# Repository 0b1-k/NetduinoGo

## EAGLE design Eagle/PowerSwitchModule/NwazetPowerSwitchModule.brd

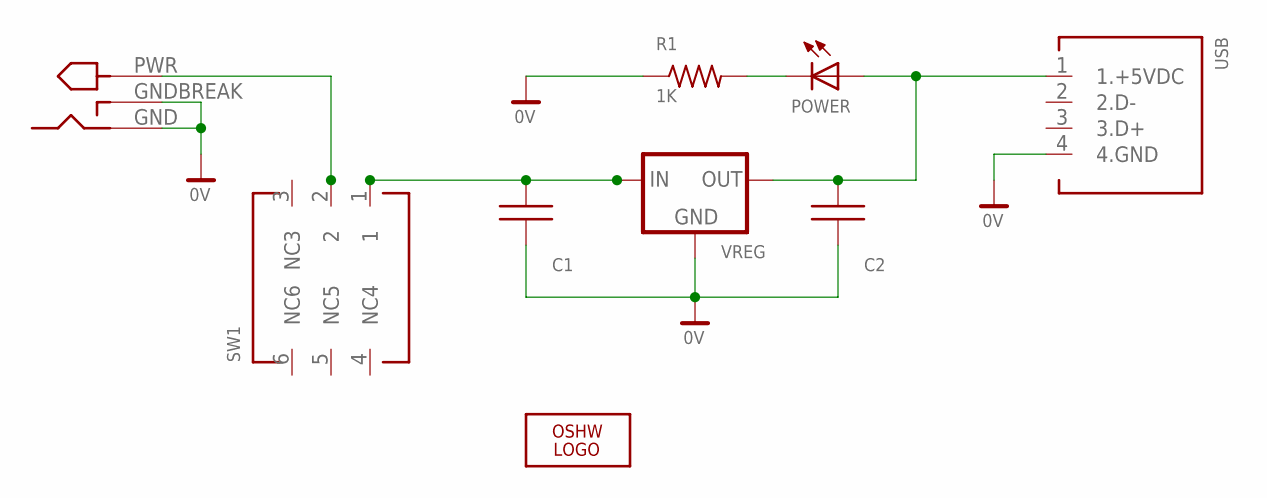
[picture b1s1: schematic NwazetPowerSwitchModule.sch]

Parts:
C1: 0.47uF; 0805
C2: MURATA_GRM_10UF_CER_0805; 0805
LOGO1: OSHW_LOGO_FILLX0100-NT; OSHW_FILLX100_NOTEXT
PJ: CUI_POWER_JACK_102A; CUI_PJ-102A
POWER: LITEON_WHITE_LED_0805; 0805
R1: 1K; 0805
SW1: CTS_065T_SPST_SLIDE_SWITCH
USB: AMPHENOL_USB_TYPE_A_FEMALE_CONNECTOR; USB_CONNECTOR_TYPE_A_FEMALE
VREG: ON_MC33269_800MA_VREG; 800MA_VREG_DPAK

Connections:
+5VDC: C2.K (2), POWER.A, USB.1 (1.+5VDC), VREG.2.VOUT (OUT)
GND: C1.A (1), C2.A (1), PJ.GND, PJ.GNDBREAK, R1.A (1), USB.4 (4.GND), VREG.1.GND_ADJ (GND)
unnamed: POWER.K (C), R1.K (2)
PWR: PJ.PWR, SW1.2
PWR_ON: C1.K (2), SW1.1, VREG.3.VIN (IN)

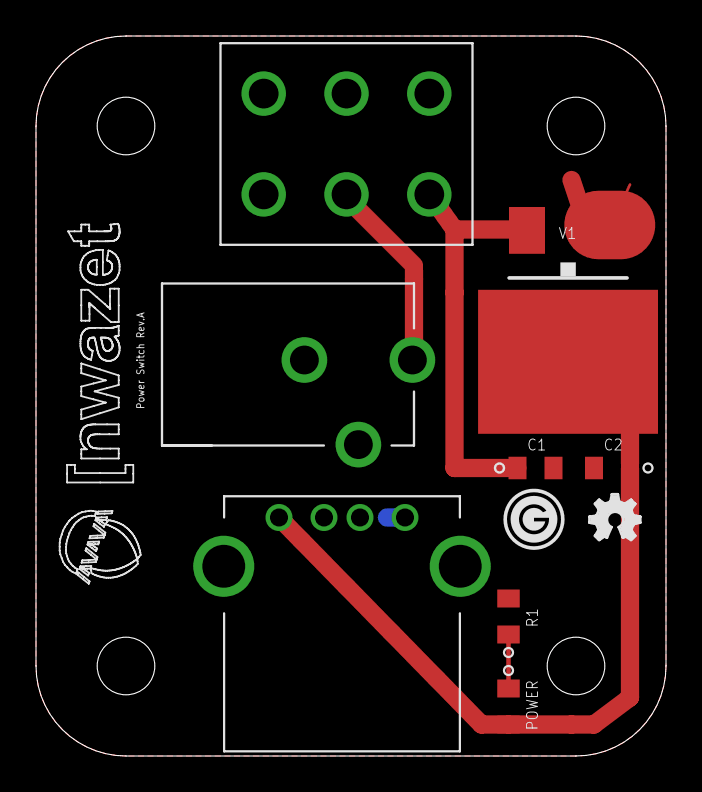
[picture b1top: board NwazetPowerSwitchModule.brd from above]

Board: 2 copper layers, 35.0 x 40.0 mm, 10 parts (0 on the bottom side), 5 nets.

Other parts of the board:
U$1: GO_LOGO

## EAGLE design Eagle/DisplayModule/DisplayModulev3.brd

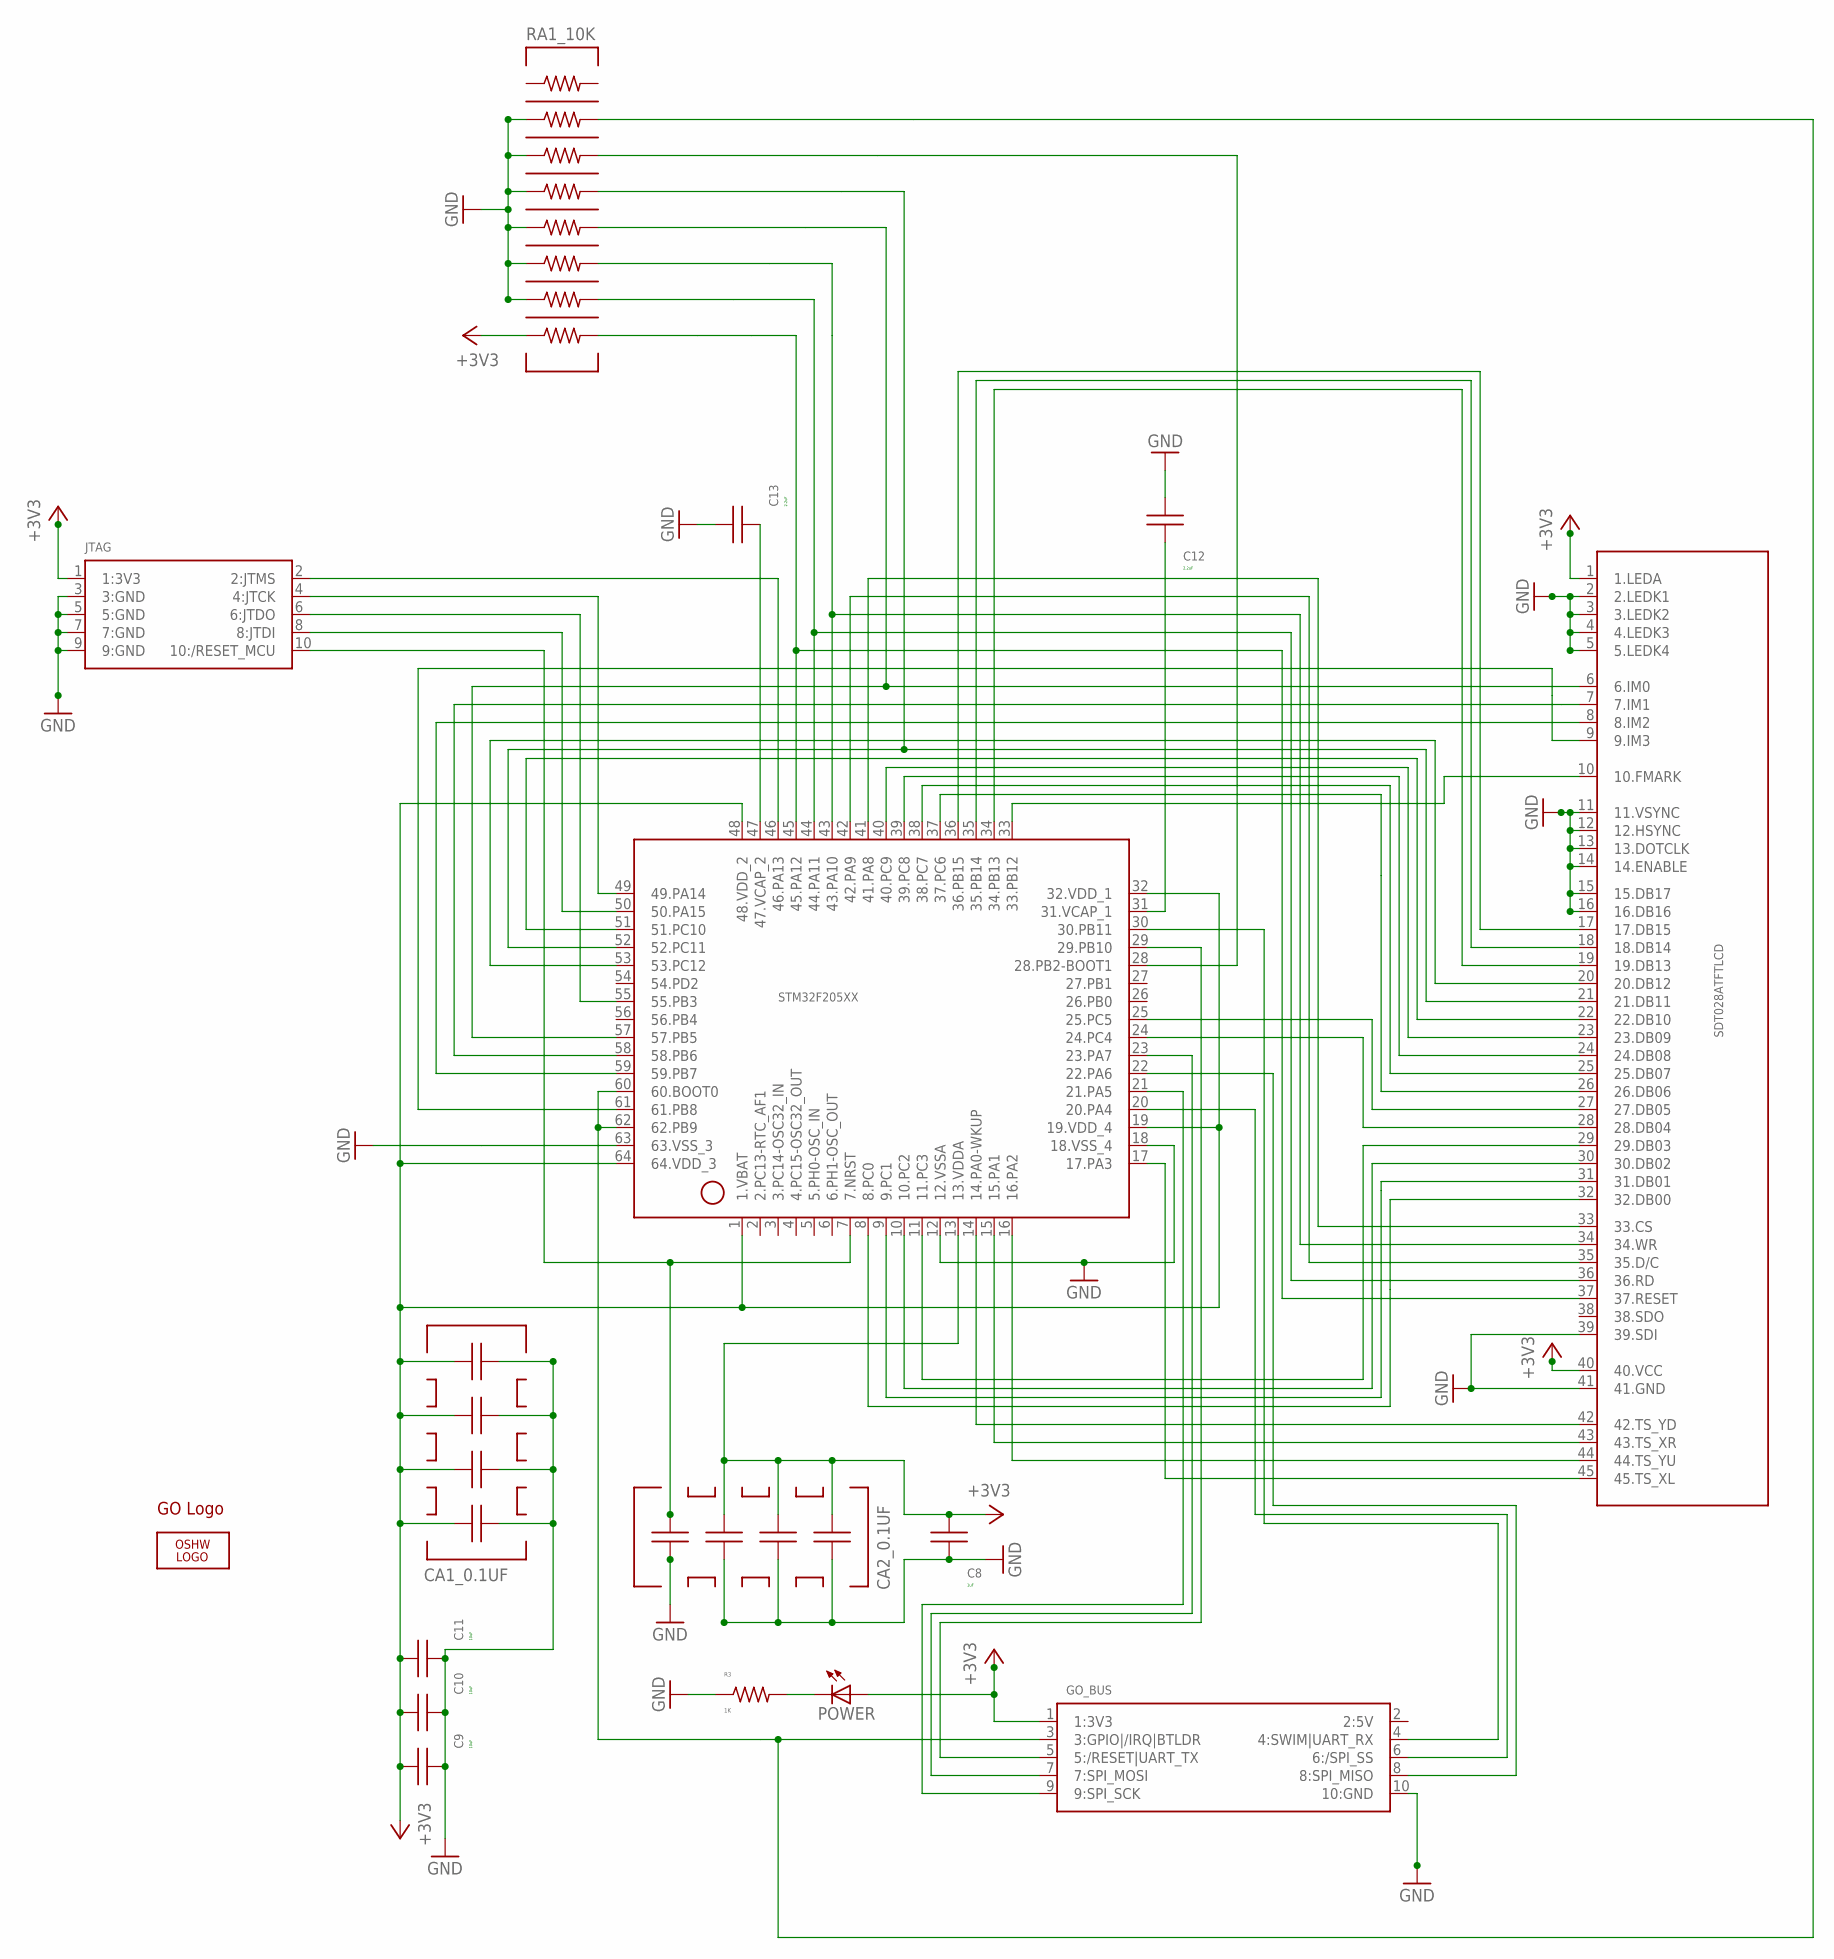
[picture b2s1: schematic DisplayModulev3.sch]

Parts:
C8: 1UF; 0805
C9, C10, C11: 10UF; 0805
C12, C13: 2.2UF; 0805
CA1_0.1UF, CA2_0.1UF: TAYIO-YUDEN_0.1UF_CAP_ARRAY_0805; TAYIO-YUDEN_CAP_ARRAY_4_CIRCUITS_0805
GO_BUS: GO_CONNECTOR; FCI-1.27X1.27MM_10PIN_HEADER_SHROUDED_SMT
JTAG: FCI-MINI_JTAG_HEADER; FCI-MINI_JTAG_CONNECTOR
LOGO1: OSHW_LOGO_FILLX0150-NT; OSHW_FILLX150_NOTEXT
POWER: LITEON_WHITE_LED_0805; 0805
R3: 1K; 0805
RA1_10K: 10K; CTS_742C163_RES_ARRAY_8_CIRCUITS_0603
SDT028ATFTLCD: HIROSE-FH12; HIROSE-FH12S-45S-0.5SH
STM32F205XX: STM32F205XXCORTEXM3RET; STM32F205XX_LQFP64
U$1: GO_LOGO

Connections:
2:5V: GO_BUS.2 (2:5V)
+3V3: C8.K (2), C9.K (2), C10.K (2), C11.K (2), CA1_0.1UF.2, CA1_0.1UF.4, CA1_0.1UF.6, CA1_0.1UF.8, CA2_0.1UF.1, CA2_0.1UF.3, CA2_0.1UF.7, GO_BUS.1 (1:3V3), JTAG.1 (1:3V3), POWER.A, RA1_10K.16, SDT028ATFTLCD.1 (1.LEDA), SDT028ATFTLCD.40 (40.VCC), STM32F205XX.1 (1.VBAT), STM32F205XX.13 (13.VDDA), STM32F205XX.19 (19.VDD_4), STM32F205XX.32 (32.VDD_1), STM32F205XX.48 (48.VDD_2), STM32F205XX.64 (64.VDD_3)
GND: C8.A (1), C9.A (1), C10.A (1), C11.A (1), C12.K (2), C13.K (2), CA1_0.1UF.1, CA1_0.1UF.3, CA1_0.1UF.5, CA1_0.1UF.7, CA2_0.1UF.2, CA2_0.1UF.4, CA2_0.1UF.6, CA2_0.1UF.8, GO_BUS.10 (10:GND), JTAG.3 (3:GND), JTAG.5 (5:GND), JTAG.7 (7:GND), JTAG.9 (9:GND), R3.A (1), RA1_10K.4, RA1_10K.6, RA1_10K.8, RA1_10K.10, RA1_10K.12, RA1_10K.14, SDT028ATFTLCD.2 (2.LEDK1), SDT028ATFTLCD.3 (3.LEDK2), SDT028ATFTLCD.4 (4.LEDK3), SDT028ATFTLCD.5 (5.LEDK4), SDT028ATFTLCD.11 (11.VSYNC), SDT028ATFTLCD.12 (12.HSYNC), SDT028ATFTLCD.13 (13.DOTCLK), SDT028ATFTLCD.14 (14.ENABLE), SDT028ATFTLCD.15 (15.DB17), SDT028ATFTLCD.16 (16.DB16), SDT028ATFTLCD.39 (39.SDI), SDT028ATFTLCD.41 (41.GND), STM32F205XX.12 (12.VSSA), STM32F205XX.18 (18.VSS_4), STM32F205XX.63 (63.VSS_3)
unnamed: JTAG.2 (2:JTMS), STM32F205XX.46 (46.PA13)
unnamed: JTAG.4 (4:JTCK), STM32F205XX.49 (49.PA14)
unnamed: JTAG.6 (6:JTDO), STM32F205XX.55 (55.PB3)
unnamed: JTAG.8 (8:JTDI), STM32F205XX.50 (50.PA15)
unnamed: CA2_0.1UF.5, JTAG.10 (10:/RESET_MCU), STM32F205XX.7 (7.NRST)
unnamed: SDT028ATFTLCD.32 (32.DB00), STM32F205XX.8 (8.PC0)
unnamed: SDT028ATFTLCD.31 (31.DB01), STM32F205XX.9 (9.PC1)
unnamed: SDT028ATFTLCD.30 (30.DB02), STM32F205XX.10 (10.PC2)
unnamed: SDT028ATFTLCD.29 (29.DB03), STM32F205XX.11 (11.PC3)
unnamed: SDT028ATFTLCD.28 (28.DB04), STM32F205XX.24 (24.PC4)
unnamed: SDT028ATFTLCD.27 (27.DB05), STM32F205XX.25 (25.PC5)
unnamed: SDT028ATFTLCD.26 (26.DB06), STM32F205XX.37 (37.PC6)
unnamed: SDT028ATFTLCD.25 (25.DB07), STM32F205XX.38 (38.PC7)
unnamed: SDT028ATFTLCD.24 (24.DB08), STM32F205XX.39 (39.PC8)
unnamed: SDT028ATFTLCD.23 (23.DB09), STM32F205XX.40 (40.PC9)
unnamed: SDT028ATFTLCD.22 (22.DB10), STM32F205XX.51 (51.PC10)
unnamed: RA1_10K.7, SDT028ATFTLCD.21 (21.DB11), STM32F205XX.52 (52.PC11)
unnamed: SDT028ATFTLCD.20 (20.DB12), STM32F205XX.53 (53.PC12)
unnamed: SDT028ATFTLCD.19 (19.DB13), STM32F205XX.34 (34.PB13)
unnamed: SDT028ATFTLCD.18 (18.DB14), STM32F205XX.35 (35.PB14)
unnamed: SDT028ATFTLCD.17 (17.DB15), STM32F205XX.36 (36.PB15)
unnamed: SDT028ATFTLCD.42 (42.TS_YD), STM32F205XX.14 (14.PA0-WKUP)
unnamed: SDT028ATFTLCD.43 (43.TS_XR), STM32F205XX.15 (15.PA1)
unnamed: SDT028ATFTLCD.44 (44.TS_YU), STM32F205XX.16 (16.PA2)
unnamed: SDT028ATFTLCD.45 (45.TS_XL), STM32F205XX.17 (17.PA3)
unnamed: SDT028ATFTLCD.8 (8.IM2), STM32F205XX.59 (59.PB7)
unnamed: RA1_10K.9, SDT028ATFTLCD.6 (6.IM0), STM32F205XX.57 (57.PB5)
unnamed: SDT028ATFTLCD.7 (7.IM1), STM32F205XX.58 (58.PB6)
unnamed: SDT028ATFTLCD.9 (9.IM3), STM32F205XX.61 (61.PB8)
unnamed: SDT028ATFTLCD.33 (33.CS), STM32F205XX.41 (41.PA8)
unnamed: SDT028ATFTLCD.35 (35.D/C), STM32F205XX.42 (42.PA9)
unnamed: RA1_10K.11, SDT028ATFTLCD.34 (34.WR), STM32F205XX.43 (43.PA10)
unnamed: RA1_10K.13, SDT028ATFTLCD.36 (36.RD), STM32F205XX.44 (44.PA11)
unnamed: RA1_10K.15, SDT028ATFTLCD.37 (37.RESET), STM32F205XX.45 (45.PA12)
unnamed: SDT028ATFTLCD.10 (10.FMARK), STM32F205XX.33 (33.PB12)
unnamed: GO_BUS.6 (6:/SPI_SS), STM32F205XX.20 (20.PA4)
unnamed: GO_BUS.9 (9:SPI_SCK), STM32F205XX.21 (21.PA5)
unnamed: GO_BUS.8 (8:SPI_MISO), STM32F205XX.22 (22.PA6)
unnamed: GO_BUS.7 (7:SPI_MOSI), STM32F205XX.23 (23.PA7)
unnamed: GO_BUS.5 (5:/RESET|UART_TX), STM32F205XX.29 (29.PB10)
unnamed: GO_BUS.4 (4:SWIM|UART_RX), STM32F205XX.30 (30.PB11)
unnamed: GO_BUS.3 (3:GPIO|/IRQ|BTLDR), RA1_10K.3, STM32F205XX.60 (60.BOOT0), STM32F205XX.62 (62.PB9)
unnamed: C12.A (1), STM32F205XX.31 (31.VCAP_1)
unnamed: C13.A (1), STM32F205XX.47 (47.VCAP_2)
unnamed: RA1_10K.5, STM32F205XX.28 (28.PB2-BOOT1)
unnamed: POWER.K (C), R3.K (2)

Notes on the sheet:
1uF
10uF
2.2uF

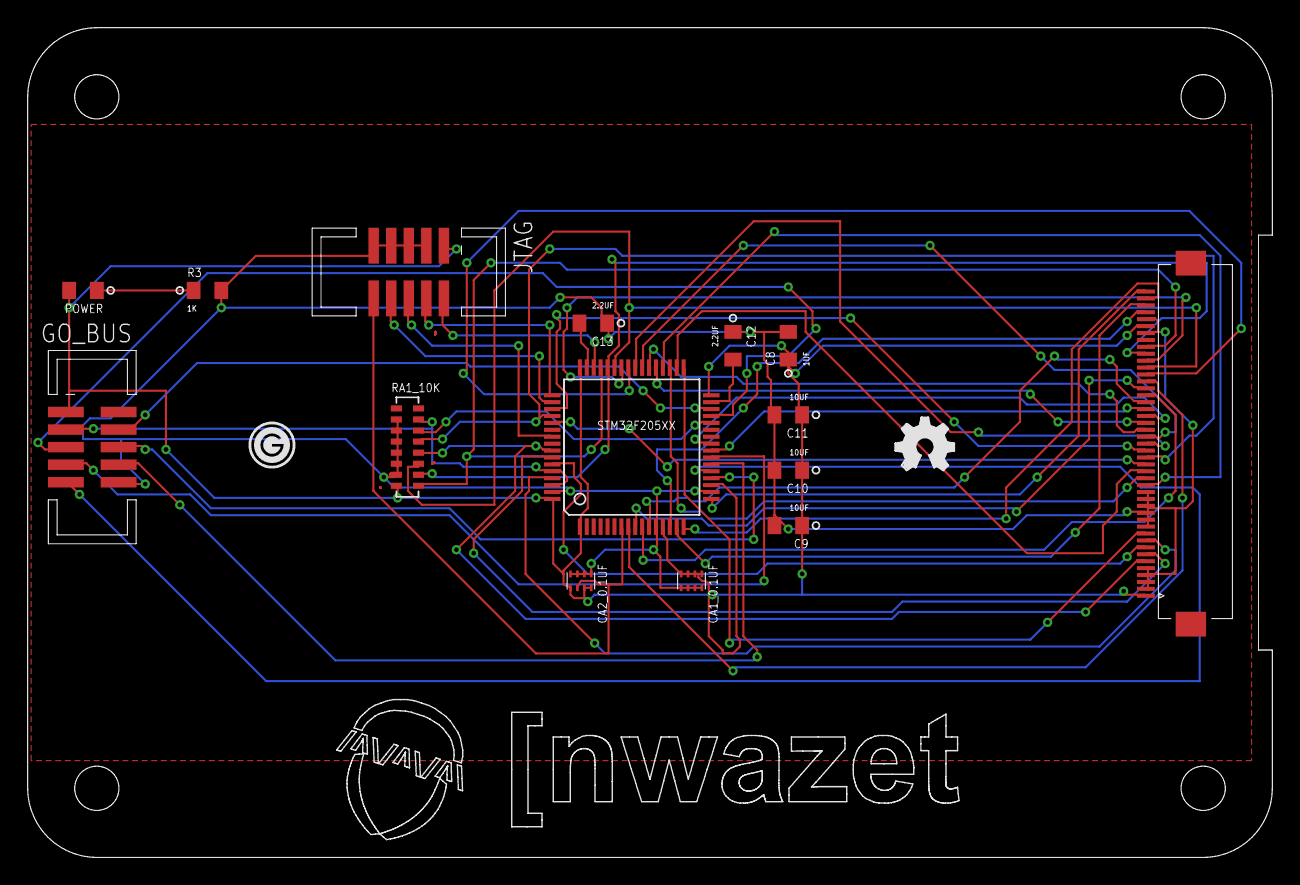
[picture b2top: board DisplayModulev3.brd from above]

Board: 2 copper layers, 90.0 x 60.0 mm, 17 parts (0 on the bottom side), 48 nets.

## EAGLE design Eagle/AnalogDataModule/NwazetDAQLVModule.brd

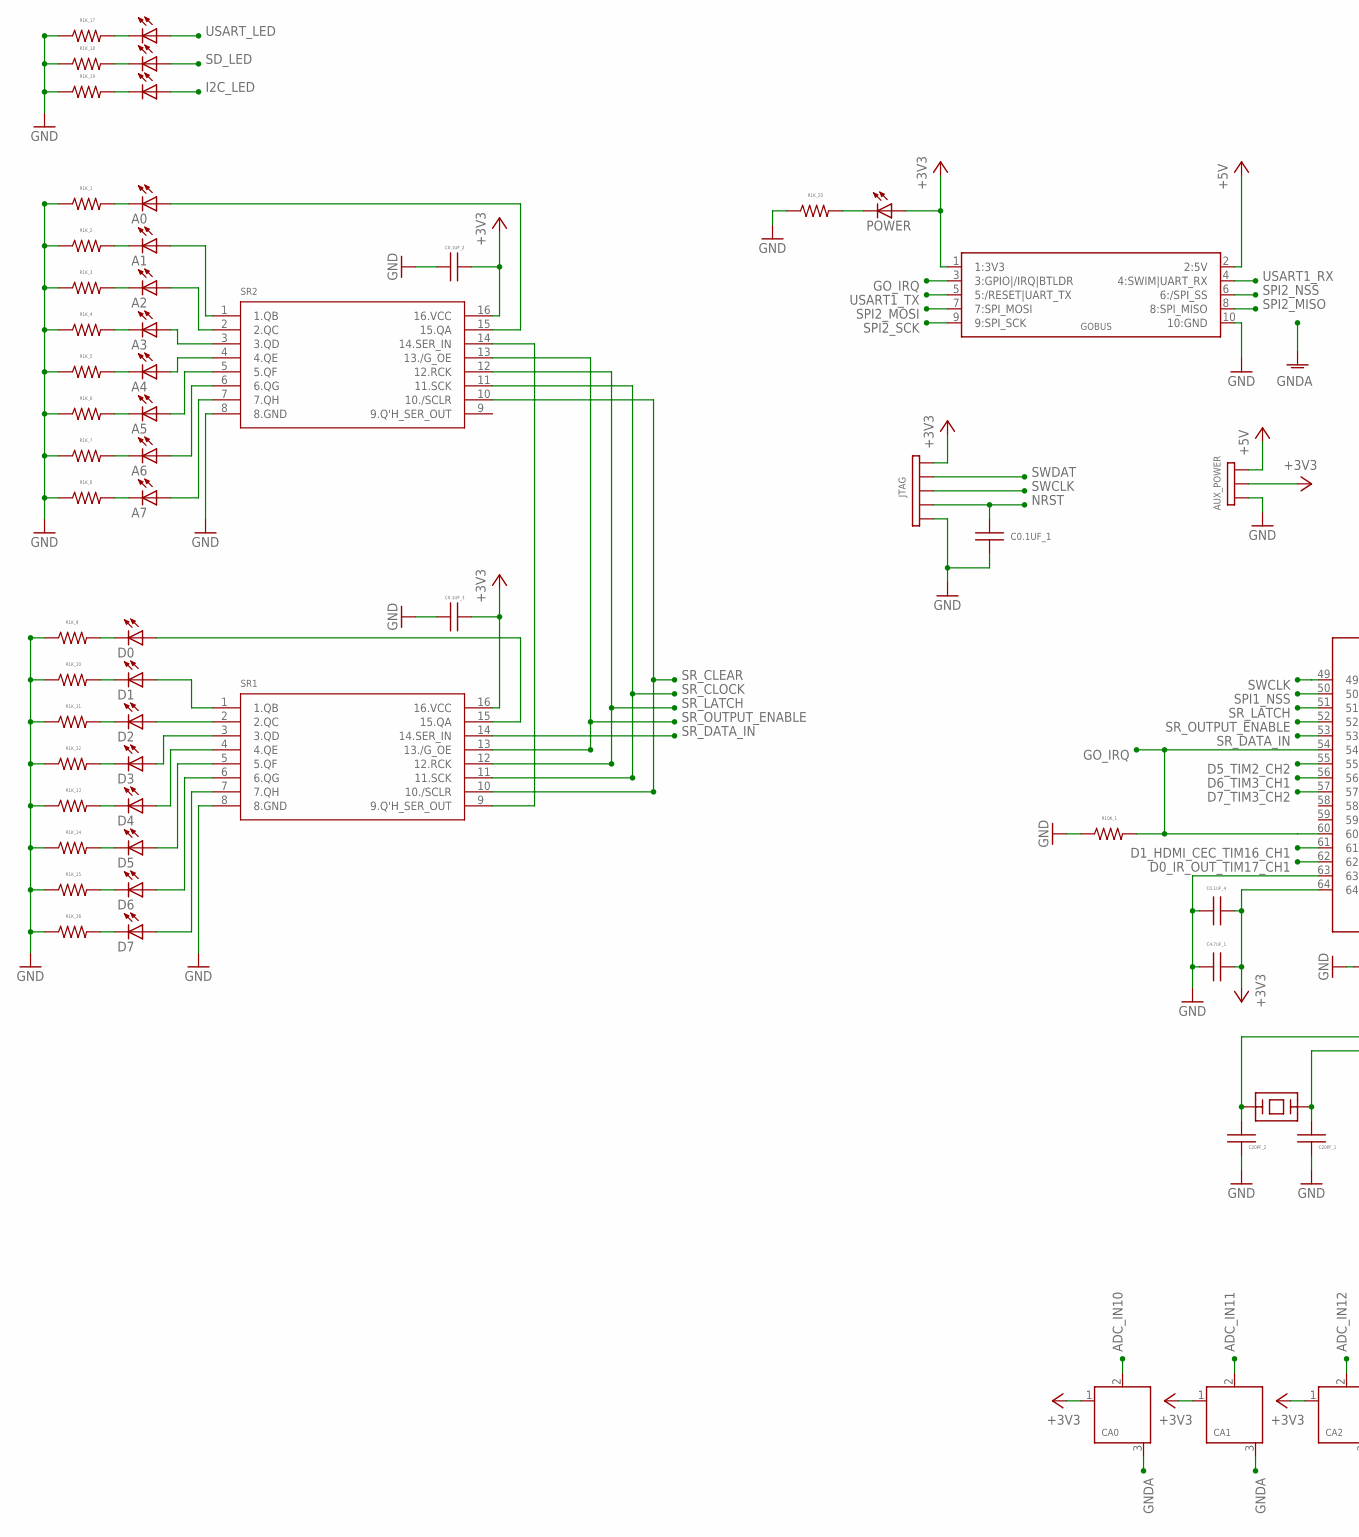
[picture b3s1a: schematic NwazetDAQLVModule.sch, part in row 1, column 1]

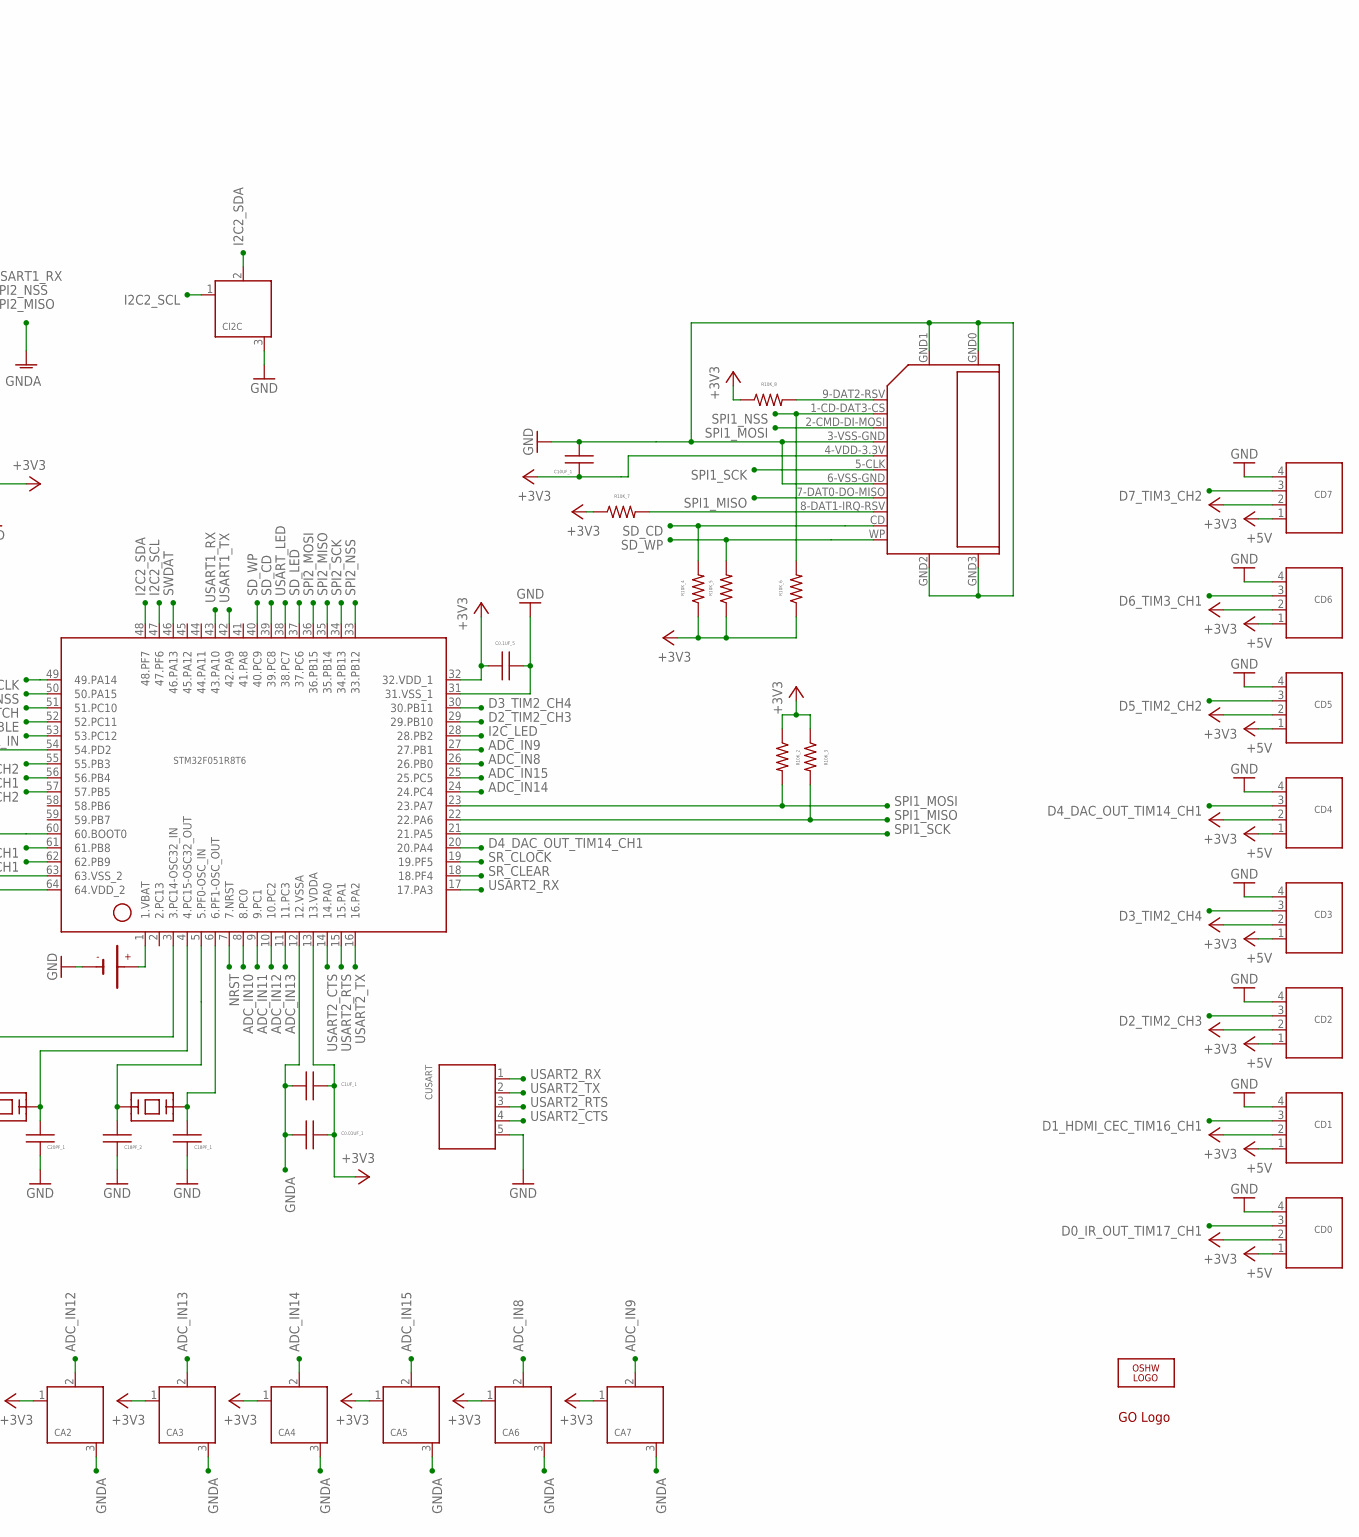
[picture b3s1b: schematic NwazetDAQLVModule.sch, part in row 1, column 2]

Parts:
A0, A1, A2, A3, A4, A5, A6, A7: LITEON_WHITE_LED_0805; 0805
AUX_POWER: POWER_HEADER_3V_5V_GND
C0.1UF_1, C0.01UF_1, C0.1UF_2, C0.1UF_3, C0.1UF_4, C0.1UF_5, C1UF_1, C4.7UF_1, C10UF_1, C18PF_1, C18PF_2, C20PF_1, C20PF_2: CAP_CER_0805; 0805_NO_POLARITY
CA0, CA1, CA2, CA3, CA4, CA5, CA6, CA7: PHOENIX_CONTACT_PCB_TERMINAL_BLOCK_3_POS_1771101; PHOENIX_CONTACT_PCB_TERMINAL_BLOCK_3_POSITIONS_1771101
CD0, CD1, CD2, CD3, CD4, CD5, CD6, CD7: PHOENIX_CONTACT_PCB_TERMINAL_BLOCK_4_POS_1771114; PHOENIX_CONTACT_PCB_TERMINAL_BLOCK_4_POSITIONS_1771114
CI2C: PHOENIX_CONTACT_PCB_TERMINAL_BLOCK_3_POS_1771101; PHOENIX_CONTACT_PCB_TERMINAL_BLOCK_3_POSITIONS_1771101
CUSART: PHOENIX_CONTACT_PCB_TERMINAL_BLOCK_5_POS_1771127; PHOENIX_CONTACT_PCB_TERMINAL_BLOCK_5_POSITIONS_1771127
D0, D1, D2, D3, D4, D5, D6, D7: LITEON_WHITE_LED_0805; 0805
GOBUS: GO_CONNECTOR; FCI-1.27X1.27MM_10PIN_HEADER_SHROUDED_SMT
I2C_LED: LITEON_WHITE_LED_0805; 0805
JTAG: PIN_HEADER_5_POSITIONS
L19: LITEON_WHITE_LED_0805; 0805
LOGO1: OSHW_LOGO_8MILX0100-NT; OSHW_8X100_NOTEXT
POWER: LITEON_WHITE_LED_0805; 0805
Q1_16MHZ: ABRACON_ABM7; ABRACON_ABM7_CERAMIC_XTAL
Q2_32.768KHZ: EPSON_MC306_32.768KHZ_CRYSTAL
R1K_1, R1K_2, R1K_3, R1K_4, R1K_5, R1K_6, R1K_7, R1K_8, R1K_9, R1K_10, R1K_11, R1K_12, R1K_13, R1K_14, R1K_15, R1K_16, R1K_17, R1K_18, R1K_19, R1K_20, R10K_1, R10K_2, R10K_3, R10K_4, R10K_5, R10K_6, R10K_7, R10K_8: RESISTOR_0805; 0805_NO_POLARITY
RTC_BATTERY: LINX_BAT-HLD-002-SMT; LINX_CR2016_SMT_BATTERY_HOLDER
SD_SOCKET: SD-101-00708-64-ND-V3; SMD-SD-SOCKET
SR1, SR2: MM74HC595; TSSOP16
STM32F051R8T6: STM32F051XXX; STM32F051XXX_LPFP64
U$2: GO_LOGO
USART_LED: LITEON_WHITE_LED_0805; 0805

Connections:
1.VBAT: RTC_BATTERY.VBAT1 (VBAT), STM32F051R8T6.1 (1.VBAT)
10KPU1: R10K_8.2, SD_SOCKET.9-DAT2-RSV
10KPU2: R10K_7.2, SD_SOCKET.8-DAT1-IRQ-RSV
+3V3: AUX_POWER.+3V3, C0.01UF_1.1, C0.1UF_2.2, C0.1UF_3.2, C0.1UF_4.1, C0.1UF_5.2, C1UF_1.1, C4.7UF_1.1, C10UF_1.1, CA0.1, CA1.1, CA2.1, CA3.1, CA4.1, CA5.1, CA6.1, CA7.1, CD0.2, CD1.2, CD2.2, CD3.2, CD4.2, CD5.2, CD6.2, CD7.2, GOBUS.1 (1:3V3), JTAG.1, POWER.A, R10K_2.1, R10K_3.1, R10K_4.1, R10K_5.1, R10K_6.1, R10K_7.1, R10K_8.1, SD_SOCKET.4-VDD-3.3V, SR1.16 (16.VCC), SR2.16 (16.VCC), STM32F051R8T6.13 (13.VDDA), STM32F051R8T6.32 (32.VDD_1), STM32F051R8T6.64 (64.VDD_2)
+5V: AUX_POWER.+5V, CD0.1, CD1.1, CD2.1, CD3.1, CD4.1, CD5.1, CD6.1, CD7.1, GOBUS.2 (2:5V)
ADC_IN8: CA6.2, STM32F051R8T6.26 (26.PB0)
ADC_IN9: CA7.2, STM32F051R8T6.27 (27.PB1)
ADC_IN10: CA0.2, STM32F051R8T6.8 (8.PC0)
ADC_IN11: CA1.2, STM32F051R8T6.9 (9.PC1)
ADC_IN12: CA2.2, STM32F051R8T6.10 (10.PC2)
ADC_IN13: CA3.2, STM32F051R8T6.11 (11.PC3)
ADC_IN14: CA4.2, STM32F051R8T6.24 (24.PC4)
ADC_IN15: CA5.2, STM32F051R8T6.25 (25.PC5)
D0_IR_OUT_TIM17_CH1: CD0.3, STM32F051R8T6.62 (62.PB9)
D1_HDMI_CEC_TIM16_CH1: CD1.3, STM32F051R8T6.61 (61.PB8)
D2_TIM2_CH3: CD2.3, STM32F051R8T6.29 (29.PB10)
D3_TIM2_CH4: CD3.3, STM32F051R8T6.30 (30.PB11)
D4_DAC_OUT_TIM14_CH1: CD4.3, STM32F051R8T6.20 (20.PA4)
D5_TIM2_CH2: CD5.3, STM32F051R8T6.55 (55.PB3)
D6_TIM3_CH1: CD6.3, STM32F051R8T6.56 (56.PB4)
D7_TIM3_CH2: CD7.3, STM32F051R8T6.57 (57.PB5)
GND: AUX_POWER.GND, C0.1UF_1.1, C0.1UF_2.1, C0.1UF_3.1, C0.1UF_4.2, C0.1UF_5.1, C4.7UF_1.2, C10UF_1.2, C18PF_1.1, C18PF_2.1, C20PF_1.1, C20PF_2.1, CD0.4, CD1.4, CD2.4, CD3.4, CD4.4, CD5.4, CD6.4, CD7.4, CI2C.3, CUSART.5, GOBUS.10 (10:GND), JTAG.5, R1K_1.1, R1K_2.1, R1K_3.1, R1K_4.1, R1K_5.1, R1K_6.1, R1K_7.1, R1K_8.1, R1K_9.1, R1K_10.1, R1K_11.1, R1K_12.1, R1K_13.1, R1K_14.1, R1K_15.1, R1K_16.1, R1K_17.1, R1K_18.1, R1K_19.1, R1K_20.1, R10K_1.1, RTC_BATTERY.GND, SD_SOCKET.3-VSS-GND, SD_SOCKET.6-VSS-GND, SD_SOCKET.GND0 (GND-0), SD_SOCKET.GND1 (GND-1), SD_SOCKET.GND2 (GND-2), SD_SOCKET.GND3 (GND-3), SR1.8 (8.GND), SR2.8 (8.GND), STM32F051R8T6.31 (31.VSS_1), STM32F051R8T6.63 (63.VSS_2)
GNDA: C0.01UF_1.2, C1UF_1.2, CA0.3, CA1.3, CA2.3, CA3.3, CA4.3, CA5.3, CA6.3, CA7.3, STM32F051R8T6.12 (12.VSSA)
GO_IRQ: GOBUS.3 (3:GPIO|/IRQ|BTLDR), R10K_1.2, STM32F051R8T6.54 (54.PD2), STM32F051R8T6.60 (60.BOOT0)
I2C2_SCL: CI2C.1, STM32F051R8T6.47 (47.PF6)
I2C2_SDA: CI2C.2, STM32F051R8T6.48 (48.PF7)
I2C_LED: I2C_LED.A, STM32F051R8T6.28 (28.PB2)
unnamed: A0.A, SR2.15 (15.QA)
unnamed: A1.A, SR2.1 (1.QB)
unnamed: A2.A, SR2.2 (2.QC)
unnamed: A3.A, SR2.3 (3.QD)
unnamed: A4.A, SR2.4 (4.QE)
unnamed: A6.A, SR2.6 (6.QG)
unnamed: A5.A, SR2.5 (5.QF)
unnamed: A7.A, SR2.7 (7.QH)
unnamed: POWER.K (C), R1K_20.2
unnamed: I2C_LED.K (C), R1K_19.2
unnamed: D7.K (C), R1K_16.2
unnamed: D6.K (C), R1K_15.2
unnamed: D5.K (C), R1K_14.2
unnamed: D0.K (C), R1K_9.2
unnamed: D1.K (C), R1K_10.2
unnamed: D2.K (C), R1K_11.2
unnamed: D3.K (C), R1K_12.2
unnamed: D0.A, SR1.15 (15.QA)
unnamed: D4.K (C), R1K_13.2
unnamed: D1.A, SR1.1 (1.QB)
unnamed: D2.A, SR1.2 (2.QC)
unnamed: A0.K (C), R1K_1.2
unnamed: A1.K (C), R1K_2.2
unnamed: A2.K (C), R1K_3.2
unnamed: D3.A, SR1.3 (3.QD)
unnamed: A3.K (C), R1K_4.2
unnamed: D4.A, SR1.4 (4.QE)
unnamed: D5.A, SR1.5 (5.QF)
unnamed: D6.A, SR1.6 (6.QG)
unnamed: D7.A, SR1.7 (7.QH)
unnamed: A4.K (C), R1K_5.2
unnamed: A5.K (C), R1K_6.2
unnamed: A6.K (C), R1K_7.2
unnamed: A7.K (C), R1K_8.2
unnamed: SR1.9 (9.Q'H_SER_OUT), SR2.14 (14.SER_IN)
NRST: C0.1UF_1.2, JTAG.4, STM32F051R8T6.7 (7.NRST)
OSC32_IN: C20PF_2.2, Q2_32.768KHZ.P$1, STM32F051R8T6.3 (3.PC14-OSC32_IN)
OSC32_OUT: C20PF_1.2, Q2_32.768KHZ.P$4, STM32F051R8T6.4 (4.PC15-OSC32_OUT)
OSC_IN: C18PF_2.2, Q1_16MHZ.P$1, STM32F051R8T6.5 (5.PF0-OSC_IN)
OSC_OUT: C18PF_1.2, Q1_16MHZ.P$2, STM32F051R8T6.6 (6.PF1-OSC_OUT)
RA5_R3: L19.K (C), R1K_18.2
RA5_R4: R1K_17.2, USART_LED.K (C)
SD_CD: R10K_4.2, SD_SOCKET.CD, STM32F051R8T6.39 (39.PC8)
SD_LED: L19.A, STM32F051R8T6.37 (37.PC6)
SD_WP: R10K_5.2, SD_SOCKET.WP, STM32F051R8T6.40 (40.PC9)
SPI1_MISO: R10K_3.2, SD_SOCKET.7-DAT0-DO-MISO, STM32F051R8T6.22 (22.PA6)
SPI1_MOSI: R10K_2.2, SD_SOCKET.2-CMD-DI-MOSI, STM32F051R8T6.23 (23.PA7)
SPI1_NSS: R10K_6.2, SD_SOCKET.1-CD-DAT3-CS, STM32F051R8T6.50 (50.PA15)
SPI1_SCK: SD_SOCKET.5-CLK, STM32F051R8T6.21 (21.PA5)
SPI2_MISO: GOBUS.8 (8:SPI_MISO), STM32F051R8T6.35 (35.PB14)
SPI2_MOSI: GOBUS.7 (7:SPI_MOSI), STM32F051R8T6.36 (36.PB15)
SPI2_NSS: GOBUS.6 (6:/SPI_SS), STM32F051R8T6.33 (33.PB12)
SPI2_SCK: GOBUS.9 (9:SPI_SCK), STM32F051R8T6.34 (34.PB13)
SR_CLEAR: SR1.10 (10./SCLR), SR2.10 (10./SCLR), STM32F051R8T6.18 (18.PF4)
SR_CLOCK: SR1.11 (11.SCK), SR2.11 (11.SCK), STM32F051R8T6.19 (19.PF5)
SR_DATA_IN: SR1.14 (14.SER_IN), STM32F051R8T6.53 (53.PC12)
SR_LATCH: SR1.12 (12.RCK), SR2.12 (12.RCK), STM32F051R8T6.51 (51.PC10)
SR_OUTPUT_ENABLE: SR1.13 (13./G_OE), SR2.13 (13./G_OE), STM32F051R8T6.52 (52.PC11)
SWCLK: JTAG.3, STM32F051R8T6.49 (49.PA14)
SWDAT: JTAG.2, STM32F051R8T6.46 (46.PA13)
USART1_RX: GOBUS.4 (4:SWIM|UART_RX), STM32F051R8T6.43 (43.PA10)
USART1_TX: GOBUS.5 (5:/RESET|UART_TX), STM32F051R8T6.42 (42.PA9)
USART2_CTS: CUSART.4, STM32F051R8T6.14 (14.PA0)
USART2_RTS: CUSART.3, STM32F051R8T6.15 (15.PA1)
USART2_RX: CUSART.1, STM32F051R8T6.17 (17.PA3)
USART2_TX: CUSART.2, STM32F051R8T6.16 (16.PA2)
USART_LED: STM32F051R8T6.38 (38.PC7), USART_LED.A

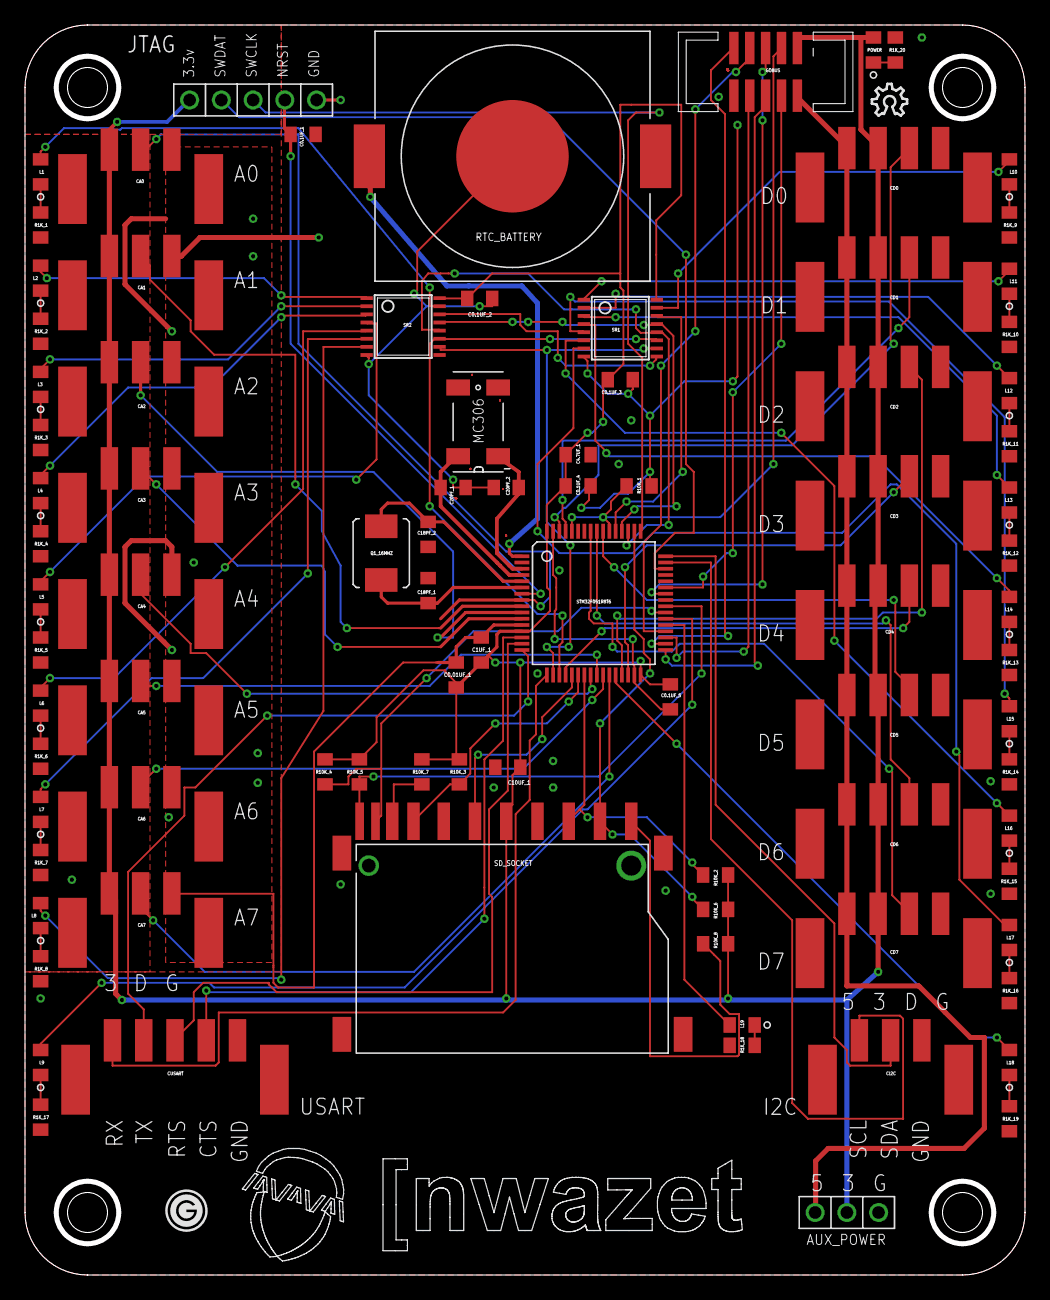
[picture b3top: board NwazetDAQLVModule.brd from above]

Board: 2 copper layers, 80.0 x 100.0 mm, 91 parts (0 on the bottom side), 94 nets.

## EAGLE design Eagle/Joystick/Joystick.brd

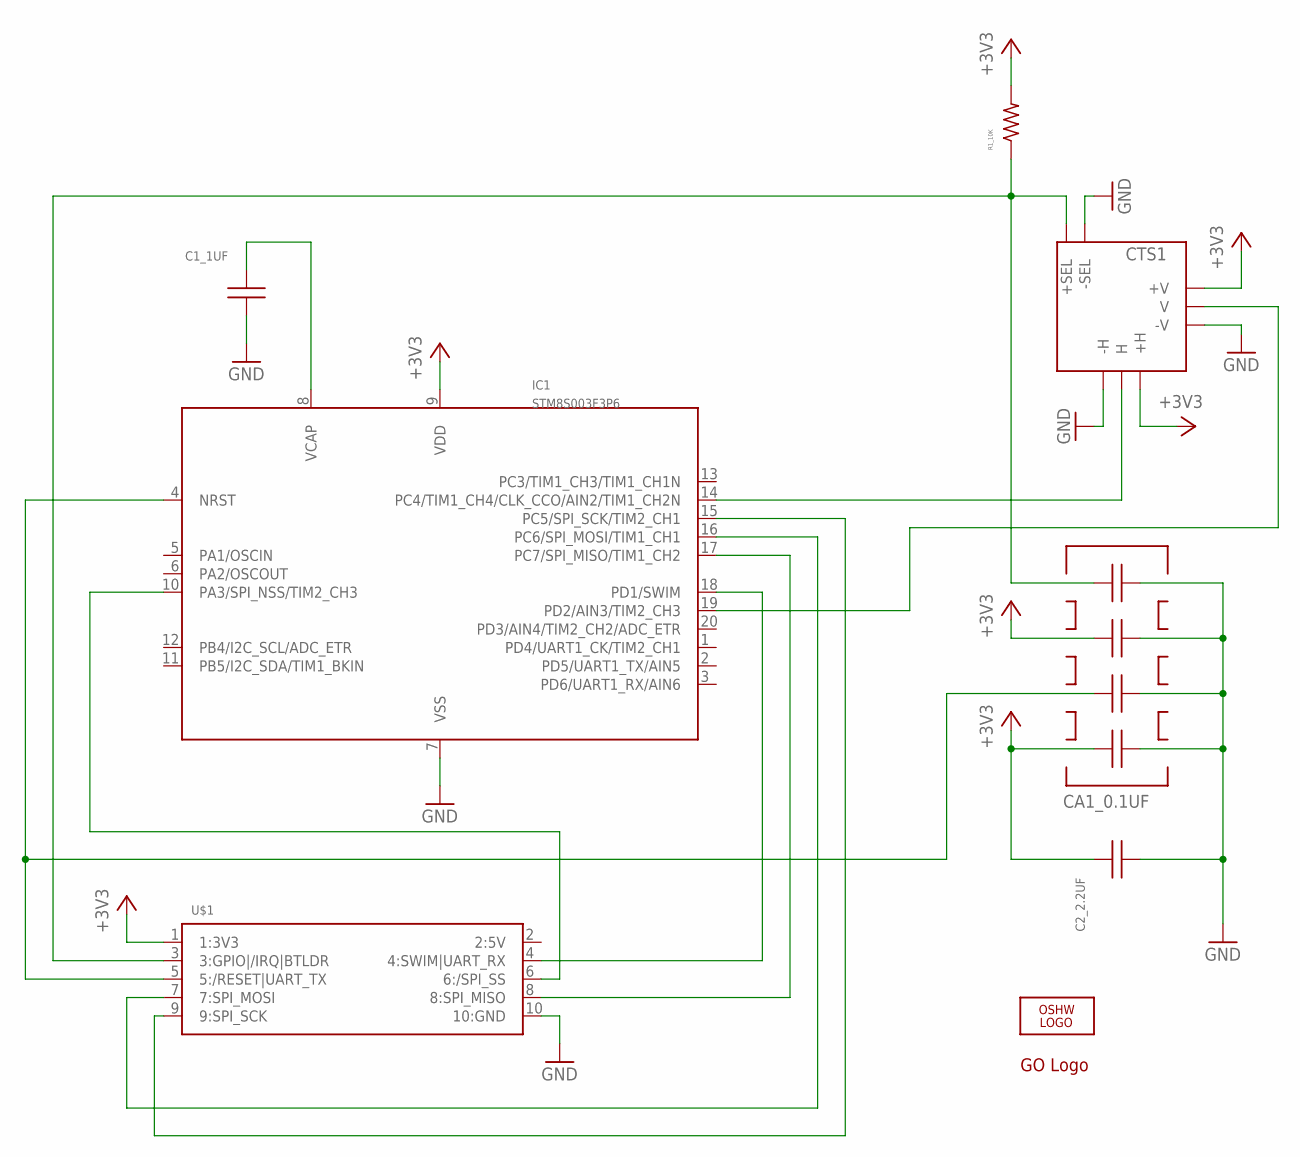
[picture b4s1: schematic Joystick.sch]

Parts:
C1_1UF: MURATA_GRM_1UF_CER_CAP_0805; 0805
C2_2.2UF: CAP_CER_2.2UF_0805; 0805
CA1_0.1UF: TAYIO-YUDEN_0.1UF_CAP_ARRAY_0805; TAYIO-YUDEN_CAP_ARRAY_4_CIRCUITS_0805
CTS1: CTS252B103A60NB10K; JOYSTICK+SWITCH
IC1: STM8S003F3P6
LOGO1: OSHW_LOGO_8MILX0150-NT; OSHW_8X150_NOTEXT
R1_10K: RESISTOR_0805; 0805
U$1: GO_CONNECTOR; FCI-1.27X1.27MM_10PIN_HEADER_SHROUDED_SMT
U$5: GO_LOGO

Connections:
2:5V: U$1.2 (2:5V)
+3V3: C2_2.2UF.A (1), CA1_0.1UF.4, CA1_0.1UF.8, CTS1.H+ (+H), CTS1.V+ (+V), IC1.9 (VDD), R1_10K.K (2), U$1.1 (1:3V3)
GND: C1_1UF.K (2), C2_2.2UF.K (2), CA1_0.1UF.1, CA1_0.1UF.3, CA1_0.1UF.5, CA1_0.1UF.7, CTS1.H- (-H), CTS1.SEL- (-SEL), CTS1.V- (-V), IC1.7 (VSS), U$1.10 (10:GND)
GOBUS_GPIO: CA1_0.1UF.6, CTS1.SEL+ (+SEL), R1_10K.A (1), U$1.3 (3:GPIO|/IRQ|BTLDR)
unnamed: IC1.10 (PA3/SPI_NSS/TIM2_CH3), U$1.6 (6:/SPI_SS)
unnamed: CA1_0.1UF.2, IC1.4 (NRST), U$1.5 (5:/RESET|UART_TX)
unnamed: IC1.18 (PD1/SWIM), U$1.4 (4:SWIM|UART_RX)
unnamed: IC1.17 (PC7/SPI_MISO/TIM1_CH2), U$1.8 (8:SPI_MISO)
unnamed: IC1.16 (PC6/SPI_MOSI/TIM1_CH1), U$1.7 (7:SPI_MOSI)
unnamed: IC1.15 (PC5/SPI_SCK/TIM2_CH1), U$1.9 (9:SPI_SCK)
unnamed: C1_1UF.A (1), IC1.8 (VCAP)
unnamed: CTS1.H-OUT (H), IC1.14 (PC4/TIM1_CH4/CLK_CCO/AIN2/TIM1_CH2N)
unnamed: CTS1.V-OUT (V), IC1.19 (PD2/AIN3/TIM2_CH3)

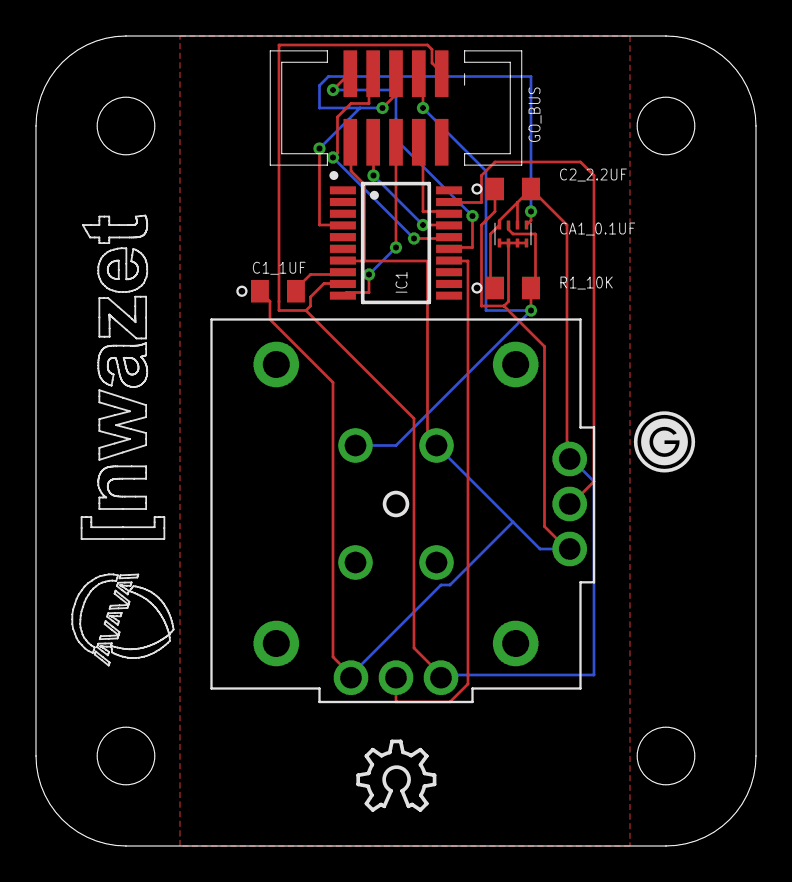
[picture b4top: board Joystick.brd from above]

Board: 2 copper layers, 40.0 x 45.0 mm, 9 parts (0 on the bottom side), 12 nets.
